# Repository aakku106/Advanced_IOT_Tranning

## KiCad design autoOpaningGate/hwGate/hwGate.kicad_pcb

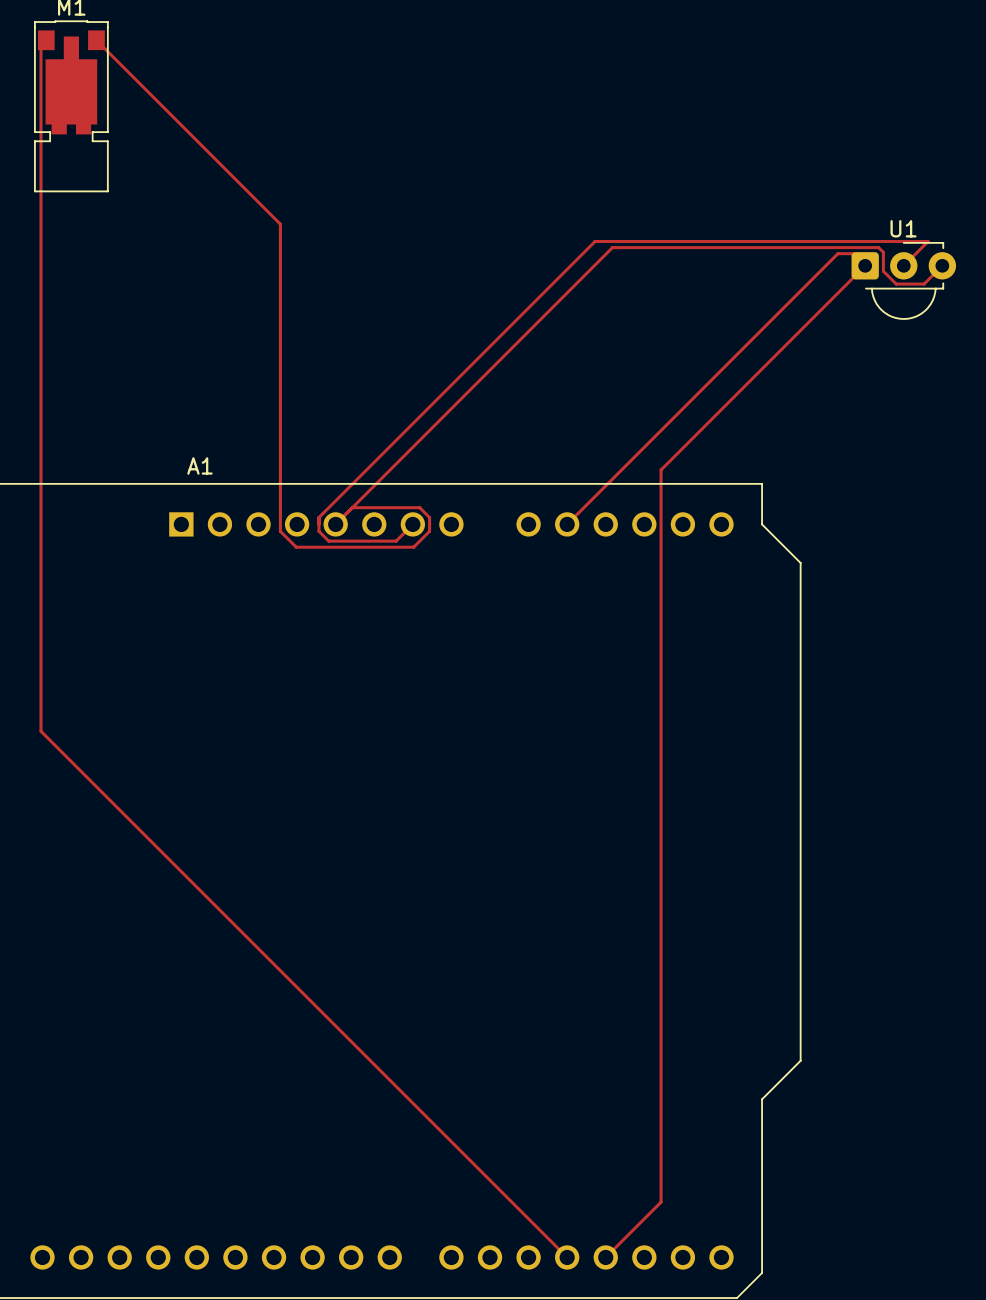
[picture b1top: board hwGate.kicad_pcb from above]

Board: 2 copper layers, 3 parts (0 on the bottom side), 4 nets.

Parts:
A1: Arduino_UNO_R3
M1: Motor_Servo; Vybronics_VZ30C1T8219732L
U1: TSSP58038; Vishay_MINICAST-3Pin

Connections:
+5V: A1.5 (+5V), M1.2 (+), U1.3 (Vs)
GND: A1.7 (GND), U1.2 (GND)
unnamed: A1.10 (A1), U1.1 (OUT)
unnamed: A1.19 (D4), M1.1 (PWM)

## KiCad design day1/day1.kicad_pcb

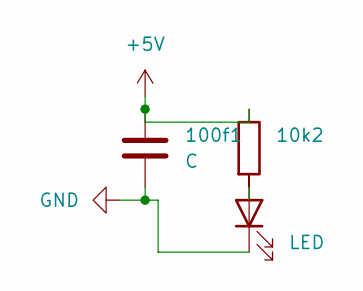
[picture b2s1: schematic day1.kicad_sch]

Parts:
10k2: R; Relay_SPST_StandexMeder_SIL_Form1B
100f1: C; CP_Axial_L10.0mm_D6.0mm_P15.00mm_Horizontal
D1: LED; LED_D3.0mm

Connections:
+5V: 10k2.1, 100f1.1
GND: 100f1.2, D1.1 (K)

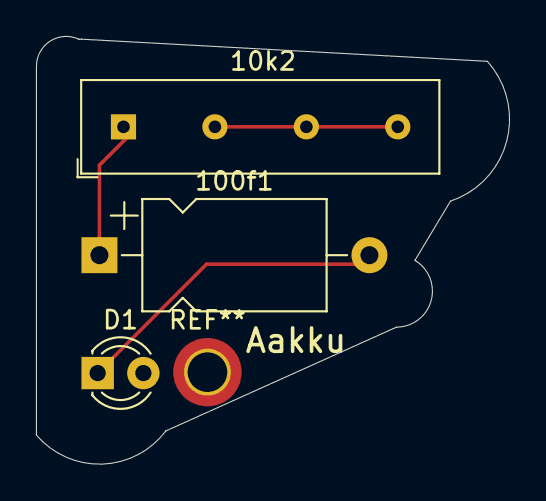
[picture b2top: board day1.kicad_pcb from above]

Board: 2 copper layers, 26.3 x 23.8 mm, 3 parts (0 on the bottom side), 2 nets.

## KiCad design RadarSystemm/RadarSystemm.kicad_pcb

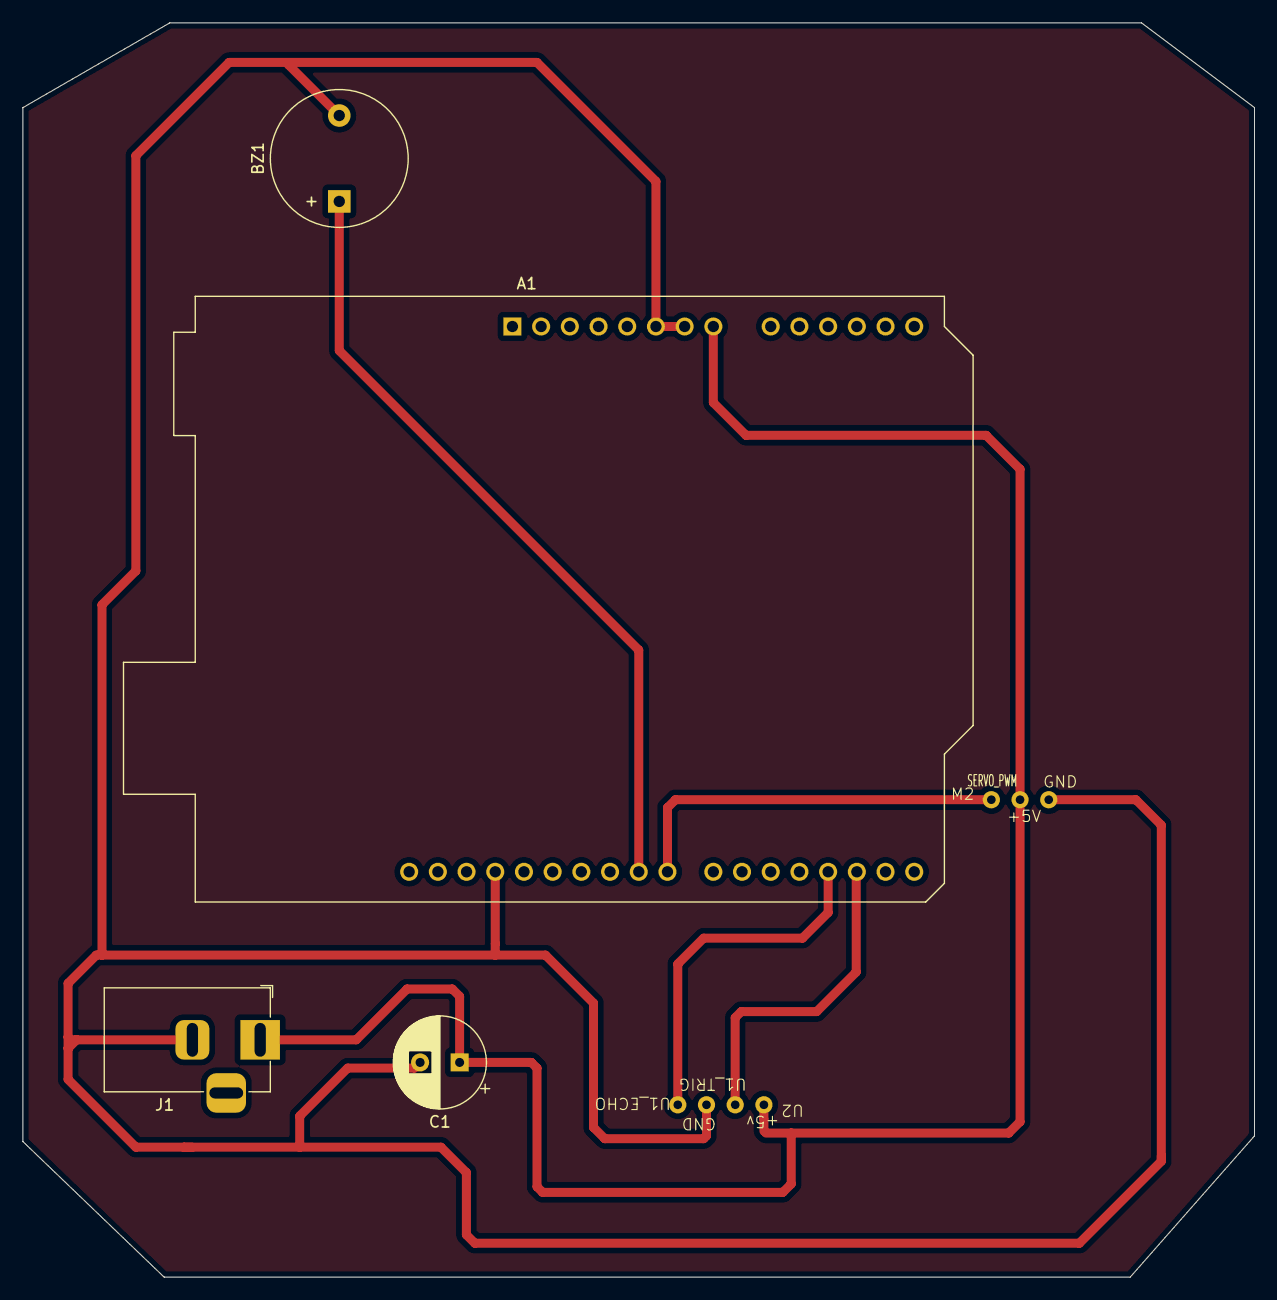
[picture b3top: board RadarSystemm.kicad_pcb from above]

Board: 2 copper layers, 109.0 x 111.0 mm, 6 parts (0 on the bottom side), 6 nets.

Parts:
A1: Arduino_UNO_R3
BZ1: Buzzer; Buzzer_12x9.5RM7.6
C1: 100μf; CP_Radial_D8.0mm_P3.50mm
J1: BarrelJack_Horizontal
M2: Conn_01x03; motor_cn
U2: Conn_01x04; ultra_mod

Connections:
+5V: A1.8 (VIN), C1.1, J1.1, M2.2, U2.1
/BUZZER: A1.24 (D9), BZ1.1 (+)
/SERVO_PWM: A1.23 (D8), M2.1
/U1_ECHO: A1.18 (D3), U2.4
/U1_TRIG: A1.17 (D2), U2.2
GND: A1.6 (GND), A1.7 (GND), A1.29 (GND), BZ1.2 (-), C1.2, J1.2, M2.3, U2.3

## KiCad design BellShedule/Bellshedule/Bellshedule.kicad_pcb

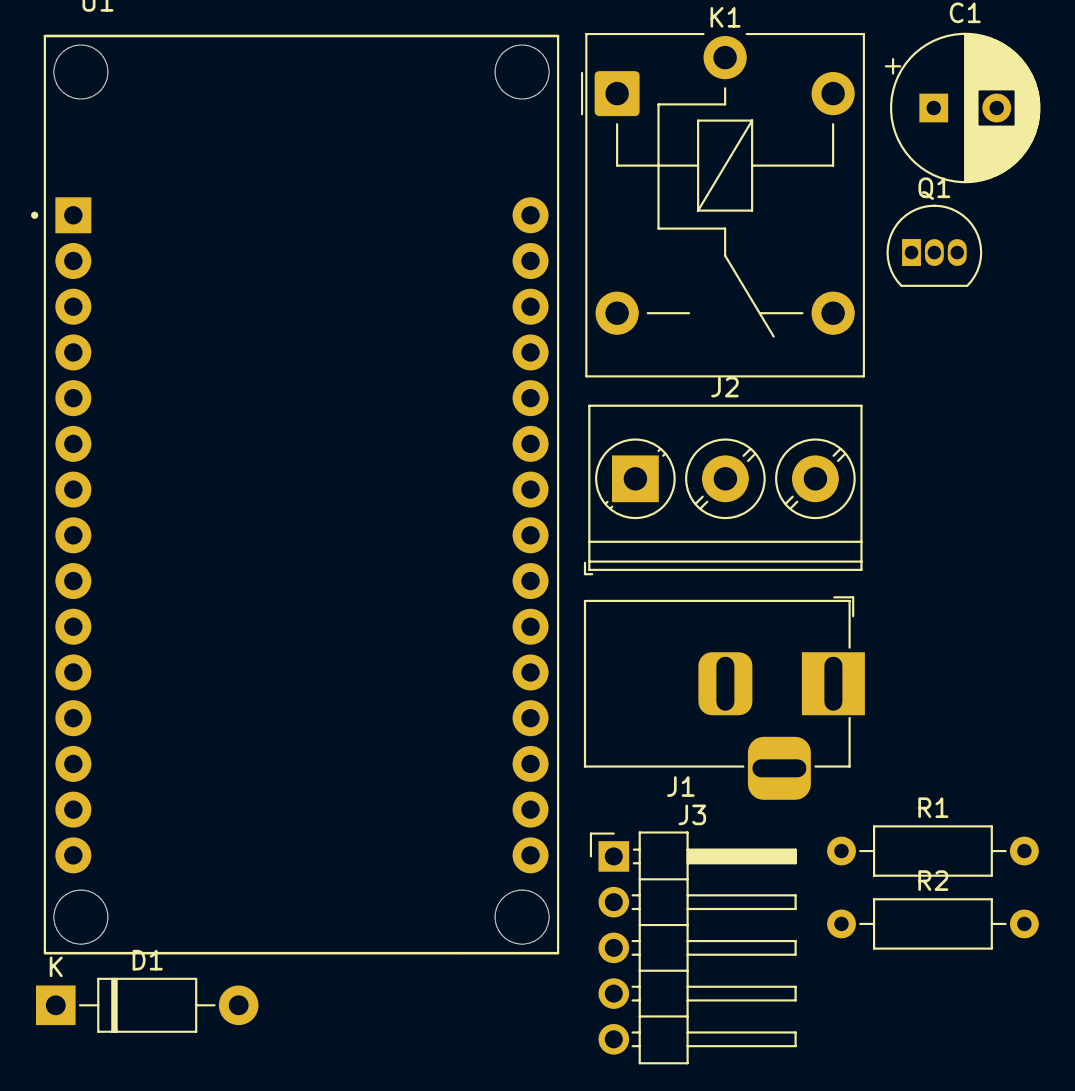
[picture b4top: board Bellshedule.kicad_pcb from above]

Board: 2 copper layers, 10 parts (0 on the bottom side), 9 nets, no tracks yet.

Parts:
C1: 100uf; CP_Radial_D8.0mm_P3.50mm
D1: 1N4007; D_DO-41_SOD81_P10.16mm_Horizontal
J1: Barrel_Jack_MountingPin; BarrelJack_Horizontal
J2: Screw_Terminal_01x03; TerminalBlock_Phoenix_PT-1,5-3-5.0-H_1x03_P5.00mm_Horizontal
J3: Conn_01x05; PinHeader_1x05_P2.54mm_Horizontal
K1: FINDER-36.11; Relay_SPDT_Finder_36.11
Q1: BC547; TO-92_Inline
R1, R2: 4K7; R_Axial_DIN0207_L6.3mm_D2.5mm_P10.16mm_Horizontal
U1: ESP32_DEVKIT_V1

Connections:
1: J2.1, K1.12
2: J2.2, K1.11
3: J2.3, K1.14
+5V: C1.1, D1.1 (K), J1.1, J3.1, K1.A1, U1.30 (VIN)
/CLK: J3.3, U1.14 (D22)
/RELAY_1: R1.1, U1.15 (D23)
GND: C1.2, J1.2, J3.2, Q1.3 (E), R2.2, U1.2 (GND), U1.29 (GND)
unnamed: D1.2 (A), K1.A2, Q1.1 (C)
unnamed: Q1.2 (B), R1.2, R2.1

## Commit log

2024-09-20 Backing up Advanced IOT tranning 2nd sem before deliting file in my ThinkPad T14 1st gen moving to my new MAC bookAir M3
